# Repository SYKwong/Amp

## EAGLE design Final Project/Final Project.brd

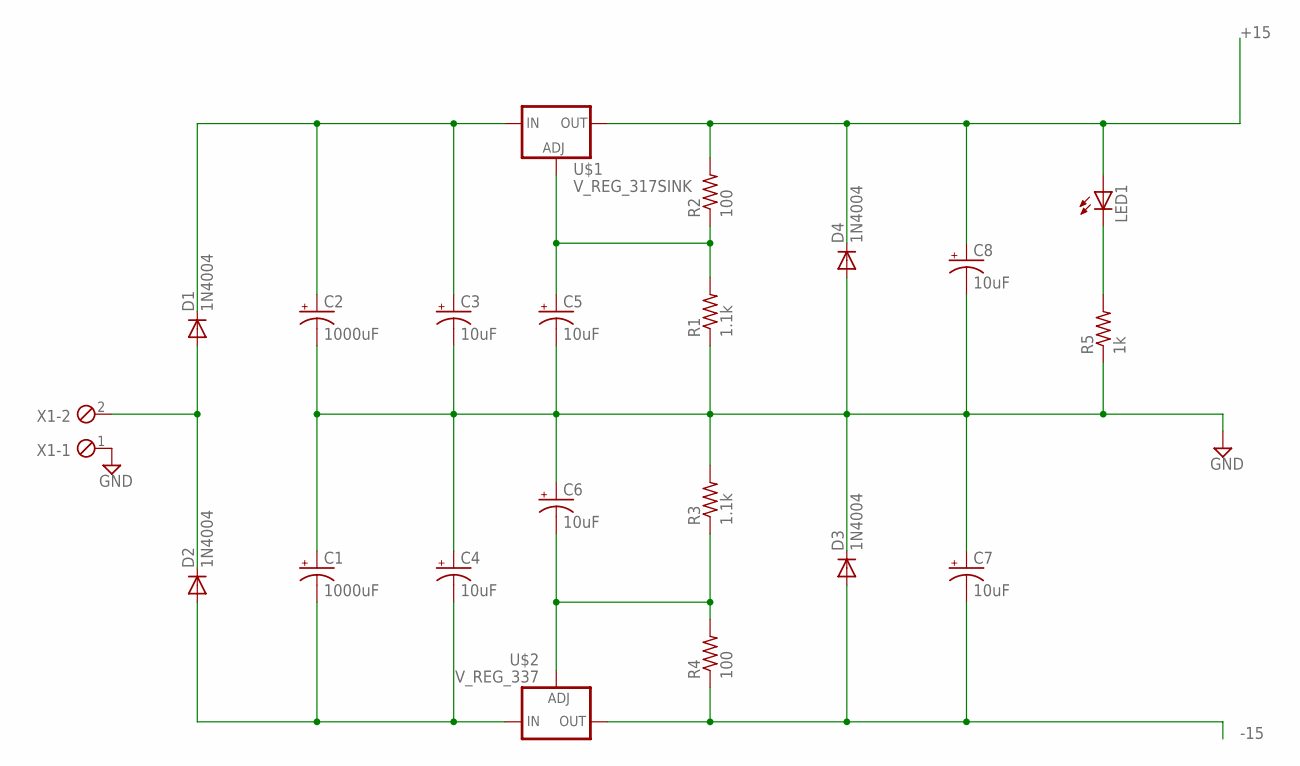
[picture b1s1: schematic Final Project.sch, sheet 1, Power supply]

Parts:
C1, C2: 1000uF; E5-10,5
C3, C4, C5, C6, C7, C8: 10uF; E2-5
D1, D2, D3, D4: 1N4004; DO41-10
LED1: LED5MM
R1, R3: 1.1k; 0204/7
R2, R4: 100; 0204/7
R5: 1k; 0204/7
U$1: V_REG_317SINK; TO220-ADJ
U$2: V_REG_337; TO220-ADJ-NEG
X1: MPT2; 2POL254

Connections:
+15: C8.+, D4.C, LED1.A, R2.2, U$1.OUT; also elsewhere on the board
-15: C7.-, D3.A, R4.1, U$2.OUT; also elsewhere on the board
GND: C1.+, C2.-, C3.-, C4.+, C5.-, C6.+, C7.+, C8.-, D3.C, D4.A, R1.1, R3.2, R5.1, X1.1; also elsewhere on the board
unnamed: C2.+, C3.+, D1.C, U$1.IN
unnamed: C5.+, R1.2, R2.1, U$1.ADJ
unnamed: D1.A, D2.C, X1.2
unnamed: C1.-, C4.-, D2.A, U$2.IN
unnamed: LED1.K (C), R5.2
unnamed: C6.-, R3.1, R4.2, U$2.ADJ

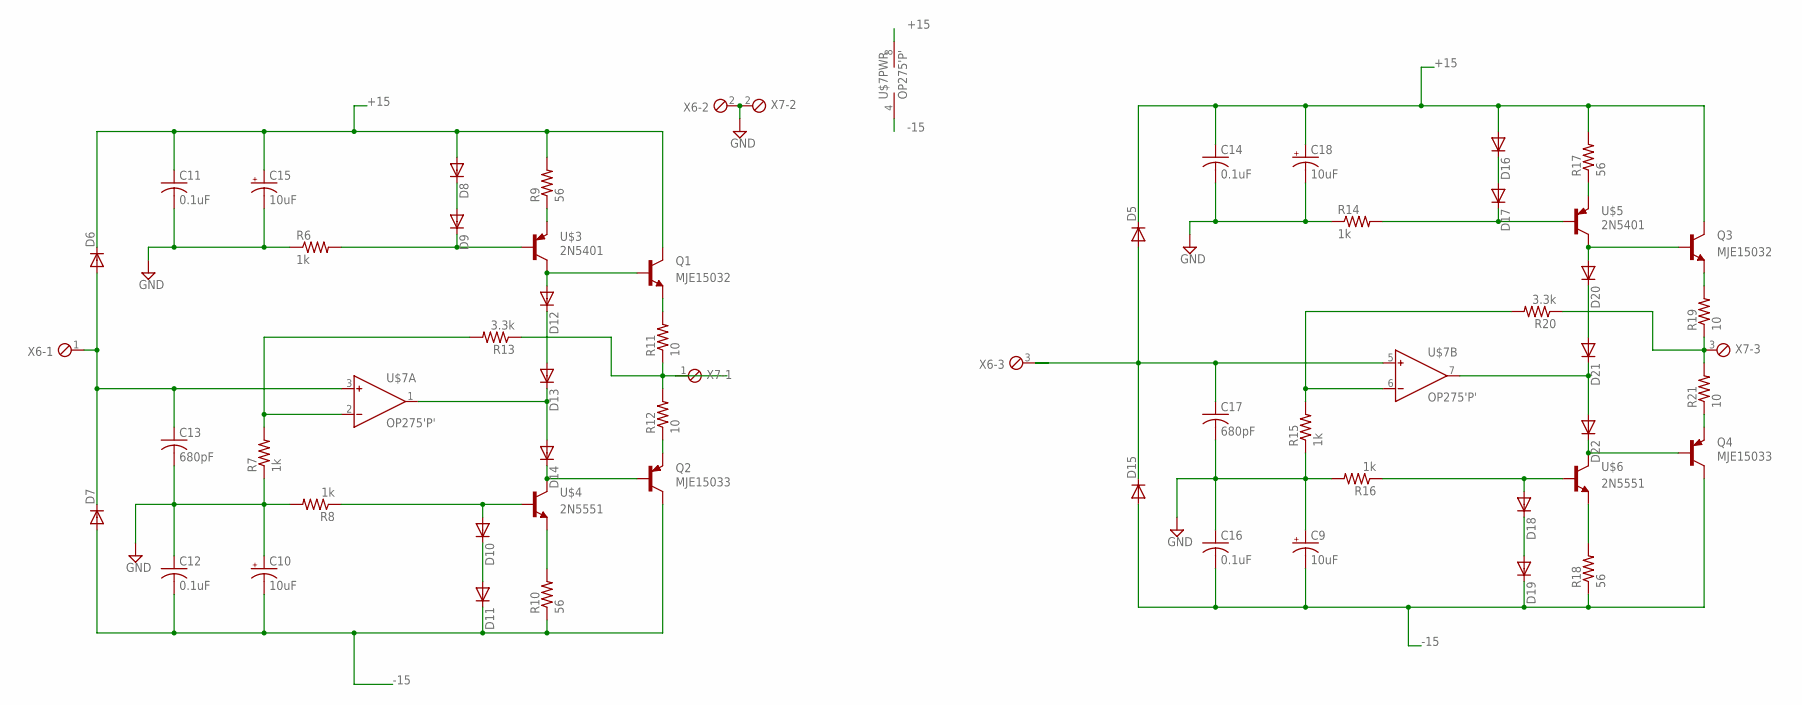
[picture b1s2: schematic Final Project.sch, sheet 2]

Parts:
C9, C10, C15, C18: 10uF; E2-5
C11, C12, C14, C16: 0.1uF; C025-025X050
C13, C17: 680pF; C025-025X050
D5, D6, D7, D8, D9, D10, D11, D12, D13, D14, D15, D16, D17, D18, D19, D20, D21, D22: 1N4148DO35-10; DO35-10
Q1, Q3: MJE15032; TO220V
Q2, Q4: MJE15033; TO220V
R6, R7, R8, R14, R15, R16: 1k; 0204/7
R9, R10, R17, R18: 56; 0204/7
R11, R12, R19, R21: 10; 0204/7
R13, R20: 3.3k; 0204/7
U$3, U$5: 2N5401
U$4, U$6: 2N5551
U$7: OP275'P'; DIL08
X6, X7: MPT3; 3POL254

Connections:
+15: C11.1, C14.1, C15.+, C18.+, D5.C, D6.C, D8.A, D16.A, Q1.2 (C), Q3.2 (C), R9.2, R17.2, U$7.8 (V+); also elsewhere on the board
-15: C9.-, C10.-, C12.2, C16.2, D7.A, D11.C, D15.A, D19.C, Q2.2 (C), Q4.2 (C), R10.1, R18.1, U$7.4 (V-); also elsewhere on the board
GND: C9.+, C10.+, C11.2, C12.1, C13.2, C14.2, C15.-, C16.1, C17.2, C18.-, R6.1, R7.1, R8.2, R14.1, R15.1, R16.2, X6.2, X7.2; also elsewhere on the board
unnamed: C13.1, D6.A, D7.C, U$7.3 (IN+), X6.1
unnamed: D10.A, R8.1, U$4.B
unnamed: Q2.3 (E), R12.1
unnamed: C17.1, D5.A, D15.C, U$7.5 (IN+), X6.3
unnamed: D16.C, D17.A
unnamed: R15.2, R20.2, U$7.6 (IN-)
unnamed: D18.A, R16.1, U$6.B
unnamed: D8.C, D9.A
unnamed: D9.C, R6.2, U$3.B
unnamed: R7.2, R13.2, U$7.2 (IN-)
unnamed: D17.C, R14.2, U$5.B
unnamed: D18.C, D19.A
unnamed: R17.1, U$5.E
unnamed: D10.C, D11.A
unnamed: R9.1, U$3.E
unnamed: D12.A, Q1.1 (B), U$3.C
unnamed: D12.C, D13.A
unnamed: D13.C, D14.A, U$7.1 (OUT)
unnamed: D14.C, Q2.1 (B), U$4.C
unnamed: R10.2, U$4.E
unnamed: Q1.3 (E), R11.2
unnamed: R11.1, R12.2, R13.1, X7.1
unnamed: D20.A, Q3.1 (B), U$5.C
unnamed: D20.C, D21.A
unnamed: D21.C, D22.A, U$7.7 (OUT)
unnamed: D22.C, Q4.1 (B), U$6.C
unnamed: R18.2, U$6.E
unnamed: Q3.3 (E), R19.2
unnamed: R19.1, R20.1, R21.2, X7.3
unnamed: Q4.3 (E), R21.1

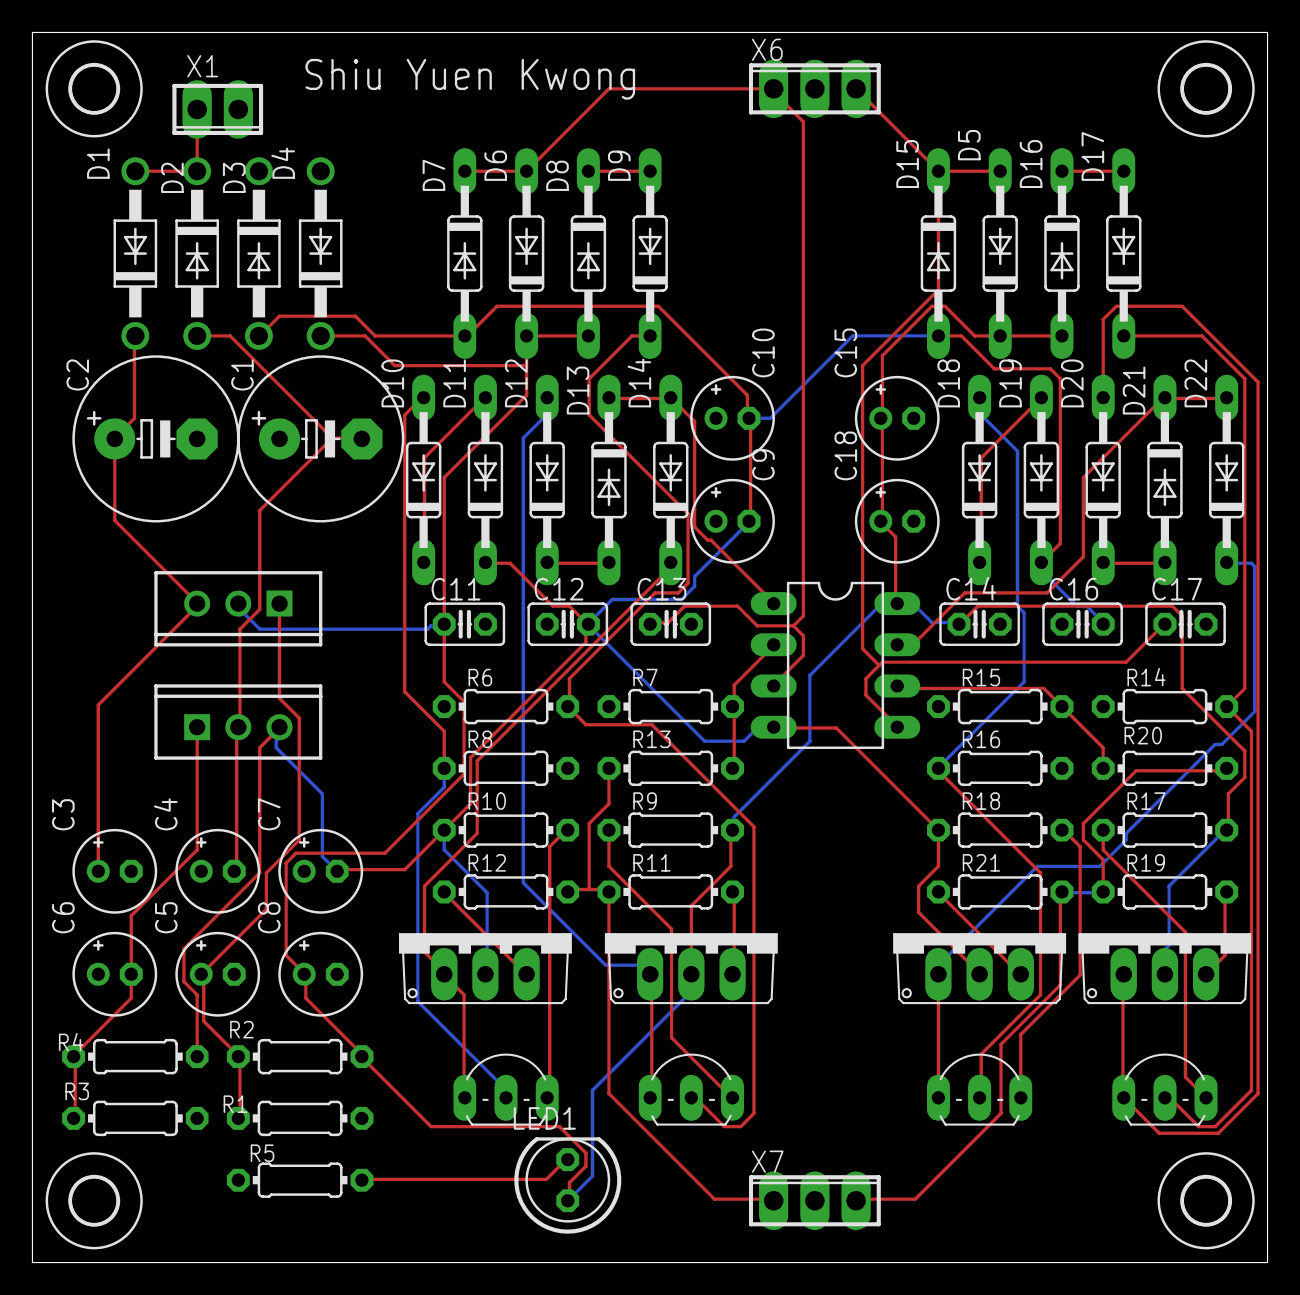
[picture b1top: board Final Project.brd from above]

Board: 2 copper layers, 76.2 x 75.9 mm, 80 parts (0 on the bottom side), 39 nets.

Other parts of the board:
U$8, U$9, U$10, U$11: 2,8
